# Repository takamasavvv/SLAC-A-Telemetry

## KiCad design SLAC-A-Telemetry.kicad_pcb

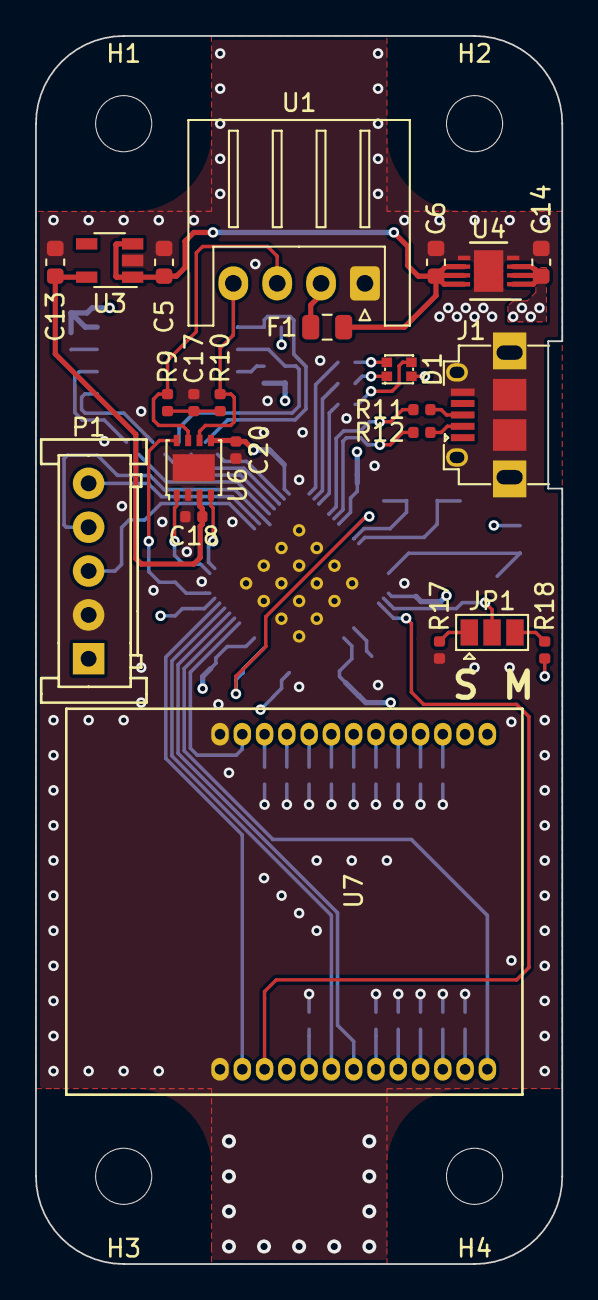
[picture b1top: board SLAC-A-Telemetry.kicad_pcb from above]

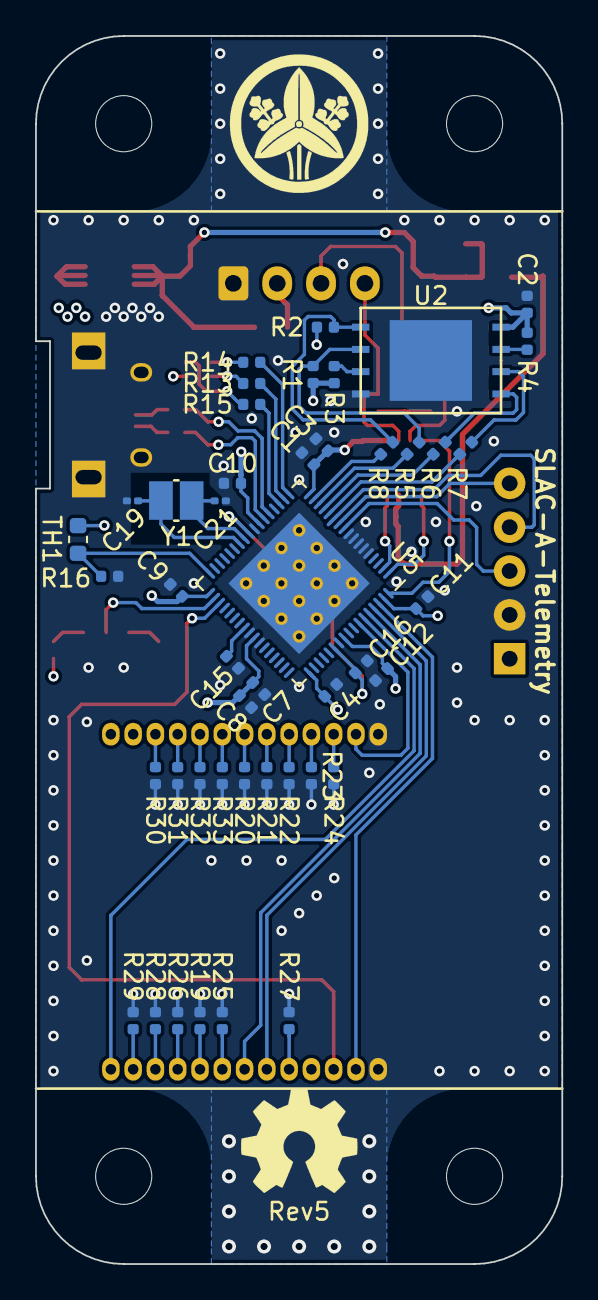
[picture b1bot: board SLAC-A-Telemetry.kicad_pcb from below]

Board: 4 copper layers, 30.0 x 70.0 mm, 72 parts (45 on the bottom side), 63 nets.

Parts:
C1, C2, C3, C4, C7, C8, C9, C11, C18, C20: 0.1uF; C_0402_1005Metric
C5, C6, C13, C14: 10uF; C_0603_1608Metric
C10, C12, C15, C16: 1uF; C_0402_1005Metric
C17: 4.7nF; C_0402_1005Metric
C19, C21: 9pF; C_0201_0603Metric
D1: LED_RGBA; LED_LiteOn_LTST-C19HE1WT
F1: Polyfuse; Fuse_0805_2012Metric
H1, H2, H3, H4: MountingHole; MountingHole_3.2mm_M3
J1: USB_B_Micro; Hirose_ZX_ZX62D-B-5P8
JP1: Jumper_3_Open; SolderJumper-3_P1.3mm_Open_Pad1.0x1.5mm
P1: KRC_Conn_SWD; JST_JQ_05JQ-BT_1x05_P2.5mm_Vertical
R1, R2, R3, R4, R17, R18: 4.7kΩ; R_0402_1005Metric
R5, R6, R7, R8, R11, R12: 22Ω; R_0402_1005Metric
R9, R10: 56Ω; R_0402_1005Metric
R13: 1.5kΩ; R_0402_1005Metric
R14, R15: 820Ω; R_0402_1005Metric
R16: 1MΩ; R_0402_1005Metric
R19, R20, R21, R22, R23, R24, R25, R26, R27, R28, R29, R30, R31, R32, R33: 47kΩ; R_0402_1005Metric
TH1: Thermistor_NTC; R_0603_1608Metric
U1: KRC_Conn_CAN; JST_XH_S4B-XH-A_1x04_P2.50mm_Horizontal
U2: W25N01GVxxIG-IT; WSON-8_8x6mm_P1.27mm
U3: LT1761-5; TSOT-23-5
U4: LT1965xDD-3.3; DFN-8-1EP_3x3mm_P0.5mm_EP1.66x2.38mm
U5: CY8C58xxLTI-LPxxx; Cypress_QFN-68_EP_8x8_Pitch0.4mm
U6: NCV7342; DFN-8-1EP_3x3mm_P0.65mm_EP1.55x2.4mm
U7: RM-92X; RFLink_Module_RM-92A
Y1: Crystal_MHz; Crystal_Murata_XRCHA

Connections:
+3V3: C1.1, C2.1, C3.1, C4.1, C7.1, C8.1, C9.1, C10.1, C11.1, C12.1, C14.1, C20.1, D1.4, R1.1, R2.1, R3.1, R4.1, R18.1, TH1.1, U2.8, U4.1, U4.2, U4.3, U5.17, U5.24, U5.35, U5.44, U5.52, U5.59, U5.67, U6.5, U7.14, U7.15
+5V: C13.1, C18.2, U3.5, U6.3
/CAN-RXD: U5.2, U6.4
/CAN-STB: U5.68, U6.8
/CAN-TXD: U5.1, U6.1
/Flash-MISO: R5.2, U5.15
/Flash-MOSI: R6.2, U5.14
/Flash-SCLK: R7.2, U5.13
/Flash-~CS: R8.2, U5.16
/LED-B: R15.2, U5.20
/LED-G: R14.2, U5.18
/LED-R: R13.2, U5.19
/Radio-CTS: U5.65, U7.6
/Radio-Config: U5.37, U7.3
/Radio-RTS: U5.64, U7.7
/Radio-RXD: U5.62, U7.25
/Radio-Role: JP1.2, U5.36
/Radio-TXD: U5.63, U7.13
/Radio-~RESET: U5.66, U7.2
/Thermistor: R16.1, TH1.2, U5.34
GND: C1.2, C2.2, C3.2, C4.2, C5.2, C6.2, C7.2, C8.2, C9.2, C10.2, C11.2, C12.2, C13.2, C14.2, C15.1, C16.1, C17.2, C18.1, C19.2, C20.2, C21.2, J1.5, J1.6, P1.2, R16.2, R17.2, R19.2, R20.2, R21.2, R22.2, R23.2, R24.2, R25.1, R26.1, R27.1, R28.1, R29.1, R30.1, R31.1, R32.1, R33.1, U1.1, U2.4, U2.9, U3.2, U4.4, U4.5, U4.9, U5.5, U5.6, U5.7, U5.8, U5.9, U5.25, U5.43, U5.45, U5.58, U5.69, U6.2, U6.9, U7.1, U7.26
unnamed: C5.1, C6.1, F1.1, U3.1, U3.3, U4.6, U4.7, U4.8
unnamed: C15.2, U5.42
unnamed: C16.2, U5.26, U5.57
unnamed: C17.1, R9.2, R10.1
unnamed: C19.1, U5.28, Y1.1
unnamed: C21.1, U5.27, Y1.2
unnamed: D1.1, R13.1
unnamed: D1.2, R14.1
unnamed: D1.3, R15.1
unnamed: F1.2, U1.2
unnamed: J1.2, R12.1
unnamed: J1.3, R11.1
unnamed: JP1.1, R17.1
unnamed: JP1.3, R18.2
unnamed: P1.3, U5.10
unnamed: P1.4, U5.12
unnamed: P1.5, U5.11
unnamed: R1.2, R5.1, U2.2
unnamed: R2.2, R8.1, U2.1
unnamed: R3.2, U2.3
unnamed: R4.2, U2.7
unnamed: R6.1, U2.5
unnamed: R7.1, U2.6
unnamed: R9.1, U1.3, U6.7
unnamed: R10.2, U1.4, U6.6
unnamed: R11.2, U5.22
unnamed: R12.2, U5.23
unnamed: R19.1, U7.9
unnamed: R20.1, U7.20
unnamed: R21.1, U7.21
unnamed: R22.1, U7.22
unnamed: R23.1, U7.23
unnamed: R24.1, U7.24
unnamed: R25.2, U7.8
unnamed: R26.2, U7.10
unnamed: R27.2, U7.5
unnamed: R28.2, U7.11
unnamed: R29.2, U7.12
unnamed: R30.2, U7.16
unnamed: R31.2, U7.17
unnamed: R32.2, U7.18
unnamed: R33.2, U7.19

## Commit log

2020-02-02 complete rev 5 (redesign to 4 layer)
